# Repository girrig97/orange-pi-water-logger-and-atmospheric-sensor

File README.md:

# Orange Pi Water Logger

This starter project logs water-condition readings to a CSV file on the Orange Pi microSD card every 6 hours.

Variant branch: this branch includes shared logger code for Orange Pi Zero 3 and Orange Pi 5 Max. The EC25-AU cellular modem, SMS alerts, server status updates, and daily status reporting are optional and are skipped automatically when no modem/SIM is detected. See [docs/orange-pi-5-max-ec25-au.md](docs/orange-pi-5-max-ec25-au.md).

On the cellular branch, SMS alert recipients can be changed from the Android app using `Get SMS Numbers` and `Save SMS Numbers`.

## Design brief

Build a field-ready freshwater monitoring recorder that can run unattended from a USB power bank, store week-by-week CSV logs on microSD, and remain usable even when individual probes or optional hardware are disconnected.

Core requirements:

- Support both Orange Pi Zero 3 and Orange Pi 5 Max as the main logger.
- Use a Raspberry Pi Pico or Pico W as the always-on low-power time and power controller.
- Power the Orange Pi only when needed for scheduled logging, download mode, pairing mode, or manual checks.
- Record freshwater sensor data every 6 hours by default.
- Switch to hourly recording when barometric pressure is low or dropping quickly.
- Store records on the Orange Pi microSD card as weekly CSV files.
- Keep logging partial records if a sensor is damaged, disconnected, or not installed.
- Tag failed sensor reads with clear status values instead of stopping the logger.
- Build a sensor baseline from early successful readings so missing optional sensors do not create repeated fault alerts.
- Allow field access from an Android phone over Bluetooth for status, time sync, live readings, CSV downloads, SMS number settings, signal checks, and test SMS.
- Make cellular reporting optional. If no EC25-AU modem or usable SIM is detected, skip SMS work and continue normal logging.
- Send optional daily SMS status, server updates, and unsafe-water alerts when the EC25-AU modem is installed and ready.

Field-use behavior:

- Power-on should automatically start the correct mode without terminal access.
- Normal wake: Pico powers the Orange Pi, the logger writes one row, sends the next interval to the Pico, syncs data, and shuts down.
- Short button press: Pico starts download mode and keeps the Orange Pi awake for Bluetooth access.
- Long button hold: Pico starts pairing mode.
- 10-second hold while awake: manual power-off fallback.
- After Bluetooth download or resume, mode markers are cleared so the next wake returns to unattended logging.

Reliability considerations:

- CSV writes are flushed and fsynced.
- Weekly CSV files reduce the impact of single-file corruption.
- The UART link between Orange Pi and Pico is required for adaptive wake timing, but logger shutdown still continues if the UART notification fails.
- All grounds must be common.
- Orange Pi GPIO and ADS1115 inputs must stay within 3.3V logic/input limits.
- Probe modules need calibration before readings should be treated as meaningful.
- The enclosure, cable glands, connectors, and sensor electronics must be protected against water ingress and condensation.

## Sensors included

- pH
- TDS
- Turbidity
- DS18B20 temperature
- ORP
- Dissolved oxygen
- Ammonium ISE
- BME280 ambient temperature, humidity, and pressure

## Calculated values

- EC from TDS
- Estimated salinity
- Water clarity percent
- Dissolved oxygen saturation percent
- Toxic ammonia NH3 estimate from ammonium, pH, and temperature
- Ammonia risk label
- Overall water score and condition label
- Ambient dew point
- Air/water temperature difference
- Adaptive next logging interval from barometric pressure

## Materials

Core computer and power:

| Qty | Item | Notes |
| ---: | --- | --- |
| 1 | Orange Pi Zero 3 or Orange Pi 5 Max | Main logger, stores CSV on microSD |
| 1 | microSD card | 16GB or larger recommended |
| 1 | Raspberry Pi Pico or Pico W | Low-power timer and download-mode button controller |
| 1 | USB power bank | 10,000mAh minimum; larger is better |
| 1 | 5V relay or MOS power-switch module | Pico-controlled switch for Orange Pi 5V; rated at least 3A, preferably 5A |
| 1 | DS3231 RTC module | Keeps accurate time for the Pico controller |
| 1 | Momentary self-reset illuminated button | Use `NO` and `C` for the button signal; LED terminals are separate |
| 1 | Weatherproof enclosure | Large enough for Orange Pi, Pico, ADCs, and wiring |

Sensor and interface modules:

| Qty | Item | Notes |
| ---: | --- | --- |
| 2 | ADS1115 ADC modules | I2C analog inputs for Orange Pi |
| 1 | pH sensor board and BNC pH probe | Analog output to ADS1115 |
| 1 | TDS sensor meter V1.0 board and probe | Analog output to ADS1115 |
| 1 | Turbidity sensor module and probe | Analog output to ADS1115 |
| 1 | Waterproof DS18B20 temperature probe | Digital 1-Wire temperature |
| 1 | ORP sensor module and BNC ORP probe | Analog output to ADS1115 |
| 1 | Gravity analog dissolved oxygen sensor kit | Analog output to ADS1115 |
| 1 | NH4+ ammonium ISE probe | BNC probe |
| 1 | High-impedance ISE interface amplifier | Required between NH4+ probe and ADS1115 |
| 1 | BME280 I2C sensor module | Ambient air temperature, humidity, and barometric pressure |

Wiring and protection:

| Qty | Item | Notes |
| ---: | --- | --- |
| 1 | 4.7k resistor | DS18B20 data pull-up to 3.3V |
| Assorted | Jumper wires or hookup wire | Use reliable connectors for field use |
| Assorted | Screw terminals or waterproof connectors | Makes sensor replacement easier |
| Assorted | Heat shrink tubing | Strain relief and insulation |
| Assorted | Cable glands | For waterproof enclosure cable exits |
| As needed | Voltage divider resistors or level shifters | Required if sensor analog output can exceed 3.3V |
| 2 | UART link wires between Orange Pi and Pico | Required for download button requests and adaptive wake timing |
| Optional | Small fuse or resettable polyfuse | Protection on 5V power line |
| Optional | Desiccant pack | Helps reduce moisture in enclosure |

Calibration and maintenance:

| Qty | Item | Notes |
| ---: | --- | --- |
| 1 set | pH buffer solutions | pH 4.00, 7.00, and 10.00 |
| 1 | TDS calibration solution | Common examples: 342ppm or 1000ppm |
| 1 | ORP calibration solution | Match your ORP probe/module instructions |
| 1 | Dissolved oxygen calibration supplies | Follow Gravity DO kit instructions |
| 1 set | NH4+ ISE calibration standards | At least two known concentrations |
| 1 | Distilled or deionized water | Rinsing probes between calibration steps |
| Optional | Cleaning/storage solutions | Especially for pH, ORP, DO, and ISE probes |

## Hardware shape

Use two ADS1115 ADC boards on the Orange Pi I2C header. The code auto-detects likely I2C buses for Orange Pi Zero 3 and Orange Pi 5 Max. Set `I2C_BUS_NUMBER` only if you want to force a specific bus.

## Wiring diagram

PCB carrier design notes are in [docs/pcb-carrier-design-brief.md](docs/pcb-carrier-design-brief.md).
The first Zero 3 KiCad carrier scaffold is in [hardware/zero3-carrier](hardware/zero3-carrier).

Key things to double-check before powering on:

- The 5V power-switch module input connects to the USB power bank 5V, not to a Pico GPIO pin.
- The 5V power-switch module GND is on the common ground bus.
- Pico `GP15` drives only the power-switch trigger / enable / signal / `IN` pin.
- Pico `GP14` connects only to the download button, not to the power switch.
- ADS1115 #1 has `ADDR -> GND` for address `0x48`.
- ADS1115 #2 has `ADDR -> 3.3V` for address `0x49`.
- Any sensor analog output above 3.3V needs level scaling before the ADS1115 input.

The numbered badges in the image match the legend table below. Recheck the power-switch section carefully before building, because relay and MOS boards use different terminal names.

Corrected numbered wiring:

| Number | Correct connection |
| --- | --- |
| 1 | USB-C/power-bank 5V to the PCB input; protected 5V feeds Pico VSYS and the MOSFET switch input |
| 2 | Common GND bus to Pico GND, power-switch GND, Orange Pi GND, ADC GND, sensor GND |
| 3 | Pico `GP15` to power-switch trigger/enable input |
| 4 | Pico `GP14` to button `NO`; button `C` to common GND |
| 5 | Pico `GP4` to DS3231 SDA |
| 6 | Pico `GP5` to DS3231 SCL |
| 7 | Pico `3V3` to DS3231 VCC |
| 8 | MOSFET switched 5V output to Orange Pi 5V input, pin 2 or 4 |
| 9 | Power-switch output/common GND to Orange Pi GND, pin 6 |
| 10 | Orange Pi pin 1 `3.3V` to ADS1115 VDD and DS18B20 VCC |
| 11 | Orange Pi pin 3 SDA to both ADS1115 SDA pins |
| 12 | Orange Pi pin 5 SCL to both ADS1115 SCL pins |
| 13 | Orange Pi pin 7 PC9/GPIO7 to DS18B20 data, with 4.7k pull-up to 3.3V |
| 14 | ADS1115 #1 A0 to pH analog output |
| 15 | ADS1115 #1 A1 to TDS analog output |
| 16 | ADS1115 #1 A2 to turbidity analog output |
| 17 | ADS1115 #1 A3 to ORP analog output |
| 18 | ADS1115 #2 A0 to dissolved oxygen analog output |
| 19 | ADS1115 #2 A1 to ammonium ISE amplifier analog output |
| 20 | ADS1115 #2 A2 spare |
| 21 | ADS1115 #2 A3 spare |

Corrected wiring view:

```text
                                  USB POWER BANK
                                5V OUT      GND
                                  |          |
                                  |          +-------------------- COMMON GND BUS
                                  |                               |
                                  v                               |
                    +-----------------------------+               |
                    | Raspberry Pi Pico / Pico W  |               |
                    |                             |               |
                    | VSYS/USB <- 5V power bank   |               |
                    | GND ------ COMMON GND BUS --+               |
                    | GP15 ---- power enable ----------------+    |
                    | GP14 ---- button NO/C ---- GND          |    |
                    | GP4  ---- DS3231 SDA                   |    |
                    | GP5  ---- DS3231 SCL                   |    |
                    | 3V3  ---- DS3231 VCC                   |    |
                    +-----------------------------+           |    |
                                                              |    |
                                  +---------------------------+    |
                                  v                                |
                         +------------------+                      |
                         | 5V POWER SWITCH   |                      |
                         | TRIG/EN <- GP15  |                      |
                         | IN+ <- bank 5V   |                      |
                         | IN- <- GND bus --+----------------------+
                         | OUT+ -> OPi 5V   |
                         | OUT- -> OPi GND  |
                         +------------------+
                                  |
                                  v
                    +-----------------------------+
                    | Orange Pi Zero 3            |
                    | Pin 2/4 5V <- switched 5V   |
                    | Pin 6 GND  -> common GND    |
                    | Pin 1 3.3V -> 3.3V rail     |
                    | Pin 3 SDA  -> I2C SDA rail  |
                    | Pin 5 SCL  -> I2C SCL rail  |
                    | Pin 7 PC9  -> DS18B20 DATA  |
                    +-----------------------------+
                         |        |        |
                         |        |        +---------------- I2C SCL rail
                         |        +------------------------- I2C SDA rail
                         +---------------------------------- 3.3V rail

      3.3V rail ----------------+----------------------+----------------------+
                                |                      |                      |
                                v                      v                      v
                    +-------------------+  +----------------------+  +----------------------+
                    | ADS1115 #1        |  | ADS1115 #2           |  | DS18B20 temp probe   |
                    | ADDR -> GND       |  | ADDR -> 3.3V/VDD     |  | Red/VCC -> 3.3V      |
                    | address 0x48      |  | address 0x49         |  | Black/GND -> GND     |
                    | VDD -> 3.3V       |  | VDD -> 3.3V          |  | Yellow/DATA -> OPi 7 |
      GND bus ---->| GND -> GND        |  | GND -> GND           |  | 4.7k DATA -> 3.3V    |
      SDA rail --->| SDA -> OPi pin 3   |  | SDA -> OPi pin 3     |  +----------------------+
      SCL rail --->| SCL -> OPi pin 5   |  | SCL -> OPi pin 5     |
                    | A0 <- pH AO        |  | A0 <- DO AO          |
                    | A1 <- TDS AO       |  | A1 <- NH4 ISE AO     |
                    | A2 <- turbidity AO |  | A2 spare             |
                    | A3 <- ORP AO       |  | A3 spare             |
                    +-------------------+  +----------------------+
                              ^     ^     ^     ^            ^          ^
                              |     |     |     |            |          |
                              |     |     |     |            |          |
       +----------------------+     |     |     |            |          |
       |                            |     |     |            |          |
+-------------+              +-------------+ +-------------+ +-------------+ +------------------+
| pH module   |              | TDS module  | | Turbidity   | | ORP module  | | Gravity DO       |
| VCC -> 5V*  |              | VCC -> 5V*  | | VCC -> 5V*  | | VCC -> 5V*  | | VCC -> 3.3-5V*   |
| GND -> GND  |              | GND -> GND  | | GND -> GND  | | GND -> GND  | | GND -> GND       |
| AO -> A0    |              | AO -> A1    | | AO -> A2    | | AO -> A3    | | AO -> ADS #2 A0  |
| BNC -> probe|              | Probe socket| | Probe socket| | BNC -> probe| | Probe socket     |
+-------------+              +-------------+ +-------------+ +-------------+ +------------------+

                          +--------------------------+
                          | NH4+ ISE interface amp   |
                          | VCC -> module requirement|
                          | GND -> common GND        |
                          | BNC -> NH4+ ISE probe    |
                          | AO  -> ADS1115 #2 A1     |
                          +--------------------------+

                          +--------------------------+
                          | DS3231 RTC module        |
                          | VCC -> Pico 3V3          |
                          | GND -> common GND        |
                          | SDA -> Pico GP4          |
                          | SCL -> Pico GP5          |
                          +--------------------------+

                          +--------------------------+
                          | Momentary button         |
                          | NO -> Pico GP14          |
                          | C  -> common GND         |
                          +--------------------------+

* If a module's analog output can exceed 3.3V, add a voltage divider or level
  scaling before the ADS1115 input.
```

All grounds must be common:

```text
Power bank GND
Pico GND
power-switch GND
Orange Pi GND
ADS1115 GND
sensor module GND
DS3231 GND
DS18B20 GND
```

Do not power the Orange Pi directly from a Pico pin. The Pico only controls the relay/MOS power-switch trigger input.

### Power switch wiring options

The code expects a simple active-high control signal:

```text
Pico GP15 HIGH -> Orange Pi power on
Pico GP15 LOW  -> Orange Pi power off
```

For a relay module, use the relay contacts to switch the Orange Pi 5V positive line:

| Relay terminal | Connect to |
| --- | --- |
| `VCC` | module supply voltage, usually 5V unless your board says otherwise |
| `GND` | common GND |
| `IN`, `SIG`, or `TRIG` | Pico `GP15` |
| `COM` | USB power bank 5V |
| `NO` | Orange Pi 5V pin 2 or 4 |
| `NC` | leave unused |

Use `NO`, not `NC`, so the Orange Pi is normally off until the Pico enables it.

For a MOS switch board, use the switched output terminals:

| MOS switch terminal | Connect to |
| --- | --- |
| `VIN+`, `V+`, or `DC+` | USB power bank 5V |
| `VIN-`, `V-`, or `DC-` | common GND |
| `TRIG`, `PWM`, `IN`, or `EN` | Pico `GP15` |
| `VOUT+`, `OUT+`, or `LOAD+` | Orange Pi 5V pin 2 or 4 |
| `VOUT-`, `OUT-`, or `LOAD-` | Orange Pi GND |

Some MOS boards are low-side switches, meaning they only switch the ground side. They can work for testing, but a relay contact or high-side switch is safer for field use because it avoids back-powering through UART or sensor wires.

## Module wiring summary

| Module | Power | Ground | Signal to Orange Pi/ADC | Probe connection |
| --- | --- | --- | --- | --- |
| pH board | 5V or module spec | common GND | AO to ADS1115 #1 A0 | pH BNC probe |
| TDS board | 5V or module spec | common GND | AO to ADS1115 #1 A1 | TDS probe socket |
| Turbidity board | 5V or module spec | common GND | AO to ADS1115 #1 A2 | turbidity probe socket |
| ORP board | 5V or module spec | common GND | AO to ADS1115 #1 A3 | ORP BNC probe |
| Gravity dissolved oxygen board | 3.3V-5V, module spec | common GND | AO to ADS1115 #2 A0 | DO probe socket |
| NH4+ ISE interface amplifier | module spec | common GND | AO to ADS1115 #2 A1 | NH4+ ISE BNC probe |
| DS18B20 waterproof temp probe | Orange Pi 3.3V | common GND | DATA to Orange Pi pin 7 | built in |
| BME280 ambient sensor | Orange Pi 3.3V | common GND | SDA pin 3, SCL pin 5 | air temp, humidity, pressure |
| ADS1115 #1 | Orange Pi 3.3V | common GND | SDA pin 3, SCL pin 5 | A0-A3 analog inputs |
| ADS1115 #2 | Orange Pi 3.3V | common GND | SDA pin 3, SCL pin 5 | A0-A3 analog inputs |
| DS3231 RTC | Pico 3.3V | common GND | SDA GP4, SCL GP5 | none |
| 5V relay or MOS power switch | power bank 5V input | common GND | trigger/EN from Pico GP15 | switched 5V to Orange Pi |
| Momentary button switch | none | `C` to common GND | `NO` to Pico GP14 | none |
| Required UART link | Orange Pi 3.3V UART logic | common GND | Orange Pi TX to Pico GP1/RX, Orange Pi RX to Pico GP0/TX | download mode and adaptive wake timing |

## Orange Pi Zero 3 header wiring

| Orange Pi physical pin | Function | Connect to |
| --- | --- | --- |
| Pin 1 | 3.3V | ADS1115 VDD, DS18B20 VCC |
| Pin 3 | I2C3 SDA | ADS1115 #1 SDA, ADS1115 #2 SDA |
| Pin 5 | I2C3 SCL | ADS1115 #1 SCL, ADS1115 #2 SCL |
| Pin 6 | GND | ADS1115 GND and all sensor GND wires |
| Pin 7 | GPIO PC9 | DS18B20 data |
| Pin 2 or 4 | 5V | Sensor boards that require 5V input |

Add a 4.7k resistor between DS18B20 data and 3.3V.

## ADS1115 address setup

| ADC board | ADDR pin | I2C address |
| --- | --- | --- |
| ADS1115 #1 | GND | `0x48` |
| ADS1115 #2 | VDD | `0x49` |

## ADS1115 sensor wiring

| Sensor | ADC input |
| --- | --- |
| pH | ADS1115 #1 A0 |
| TDS | ADS1115 #1 A1 |
| Turbidity | ADS1115 #1 A2 |
| ORP | ADS1115 #1 A3 |
| Dissolved oxygen | ADS1115 #2 A0 |
| Ammonium ISE interface | ADS1115 #2 A1 |

The ammonium ISE needs a high-impedance ISE interface board. Do not connect the electrode directly to the ADC.

Important: if the ADS1115 boards are powered from 3.3V, every analog input must stay between 0V and 3.3V. If a sensor board outputs 0-5V, use a voltage divider or level-scaling circuit before the ADS1115 input.

## Orange Pi setup

Enable I2C3:

```bash
sudo orangepi-config
```

Then go to `System`, `Hardware`, enable `ph-i2c3`, save, and reboot.

After reboot, check the ADC boards. For a Zero 3 this is usually bus 3; for a 5 Max use the bus you enabled, or run `ls /dev/i2c-*` and scan the likely buses:

```bash
sudo apt update
sudo apt install -y i2c-tools python3-smbus
i2cdetect -y 3
```

You should see:

```text
0x48
0x49
```

The code reads ADS1115 #1 at `0x48` and ADS1115 #2 at `0x49`. If `I2C_BUS_NUMBER` is unset, it auto-detects likely Orange Pi I2C buses.

## BME280 ambient sensor

Wire the BME280 to the same Orange Pi I2C bus as the ADS1115 boards:

| BME280 pin | Orange Pi header function |
| --- | --- |
| VCC/VIN | Pin 1 `3.3V` |
| GND | Pin 6 `GND` |
| SDA | Pin 3 `I2C SDA` |
| SCL | Pin 5 `I2C SCL` |

The BME280 usually appears at `0x76` or `0x77`. The logger tries both.

Install the Python libraries:

```bash
sudo apt install -y python3-pip
pip3 install smbus2 RPi.bme280 pyserial
```

The CSV adds:

```text
air_temperature_c
air_humidity_percent
air_pressure_hpa
dew_point_c
air_water_temp_difference_c
next_interval_seconds
```

## Sensor fault handling

If a sensor is damaged, disconnected, or not responding, the logger keeps running. The affected raw value and dependent calculated values are left blank in the CSV, and the matching status column explains why.

Status columns include:

```text
temperature_status
ph_status
tds_status
turbidity_status
orp_status
dissolved_oxygen_status
ammonium_ise_status
air_sensor_status
```

Common status tags:

| Tag | Meaning |
| --- | --- |
| `ok` | Sensor reading worked |
| `ds18b20_not_found` | Temperature probe was not detected |
| `ds18b20_crc_failed` | Temperature probe responded with a bad checksum |
| `ads1115_0x48_not_found_or_i2c_failed` | First ADS1115 board did not respond |
| `ads1115_0x49_not_found_or_i2c_failed` | Second ADS1115 board did not respond |
| `ads1115_0x48_channel_0_read_failed` | Specific ADC channel read failed |
| `partial_read_failure` | Some samples worked and some failed |
| `bme280_not_found_or_not_responding` | Ambient air sensor did not respond |
| `bme280_library_missing` | BME280 Python library is not installed |

Example: if the ORP probe board is disconnected, `orp_voltage` and `orp_mv` will be blank, while `orp_status` will explain the fault.

## Adaptive low-pressure logging

By default:

```text
pressure >= 1000 hPa -> next recording in 6 hours
pressure < 1000 hPa  -> next recording in 1 hour
pressure drop >= 6 hPa over recent 24h -> next recording in 1 hour
```

The Orange Pi writes the next interval to:

```text
/home/orangepi/water-logger/records/next_interval_seconds.txt
```

The UART link is required. The Pico uses it to request download mode, and after each reading the Orange Pi sends the next wake interval back to the Pico:

```text
NEXT_INTERVAL=3600
```

or:

```text
NEXT_INTERVAL=21600
```

Required UART wiring:

| Signal | Connect |
| --- | --- |
| Orange Pi UART TX | Pico GP1/RX |
| Orange Pi UART RX | Pico GP0/TX |
| Orange Pi GND | Pico GND |

The logger records the row even if this UART link is unavailable, then logs a warning and continues shutdown so the power bank is not drained. The Pico treats a missing `NEXT_INTERVAL` as a fault and retries in 1 hour. The code defaults to Orange Pi serial port `/dev/ttyS5`. If your enabled UART appears under another name, set:

```bash
export PICO_SERIAL_PORT=/dev/ttyS1
```

For I2C, auto-detection usually avoids board-specific edits. To force a bus:

```bash
export I2C_BUS_NUMBER=3   # common Zero 3 setup
export I2C_BUS_NUMBER=5   # example 5 Max setup
```

## microSD record path

Records are stored beside the project in a `records` folder. The logger starts a new CSV file each ISO calendar week to keep files smaller and reduce the impact of any single-file corruption.

If the project is copied to:

```text
/home/orangepi/water-logger
```

weekly CSV files will be created like:

```text
/home/orangepi/water-logger/records/water_conditions_2026_week_20.csv
/home/orangepi/water-logger/records/water_conditions_2026_week_21.csv
```

The download-mode marker lives in the same folder:

```text
/home/orangepi/water-logger/records/DOWNLOAD_MODE
```

## Run

```bash
python3 water_logger.py
```

The CSV files will be created as weekly files:

```text
water_conditions_YYYY_week_WW.csv
```

on the microSD card.

## Low power mode

For USB power bank use, run one reading at a time:

```bash
python3 water_logger.py --once
```

Then schedule it every 6 hours with a systemd timer or cron job. This avoids keeping the Python program awake all day, although the Orange Pi itself is still powered unless you add timed power-control hardware.

Example cron line:

```cron
0 */6 * * * /usr/bin/python3 /home/orangepi/water_logger.py --once
```

For much longer battery life, use a timer power switch, RTC power module, or small microcontroller to turn the Orange Pi on every 6 hours, let it log once, then shut it down.

With timed power hardware, run:

```bash
python3 water_logger.py --once --shutdown-after
```

## Pico power controller

Use `pico_power_controller.py` on a Raspberry Pi Pico or Pico W to switch Orange Pi power.

| Pico pin | Connect to |
| --- | --- |
| GP15 | On-board MOSFET/load-switch gate-driver input |
| GP14 | Momentary button `NO`; button `C` to GND |
| GP0/TX | Orange Pi UART RX |
| GP1/RX | Orange Pi UART TX |
| GP4 | DS3231 SDA |
| GP5 | DS3231 SCL |
| GP13 | Strongly recommended: Orange Pi ready/shutdown GPIO |
| 3V3 | DS3231 VCC |
| GND | DS3231 GND, button `C`, MOSFET gate-driver GND |
| VSYS or 5V USB input | Always-on protected 5V from the board USB-C input |

One USB-C PD input can power both the Pico and Orange Pi Zero 3. Wire it as:

```text
USB-C PD input -> PD sink controller -> negotiated 9V rail
USB-C PD input -> PD sink controller -> buck regulator -> Pico always-on 5.1V/VSYS
USB-C PD input -> PD sink controller -> buck regulator -> high-side MOSFET -> Orange Pi 5V input
```

The Pico stays powered all the time. The Orange Pi 5V input is powered only
through the MOSFET/load-switch path. For the PCB version, use a USB-C PD sink
controller and a 5A buck regulator so the board can request 9V from the power
bank and generate its own stable 5.1V rail. A 30W or larger USB-C PD power bank
is the sensible minimum for the Zero 3 build.

Normal mode:

- Pico powers the Orange Pi every 6 hours.
- Orange Pi runs `water_logger.py --once --shutdown-after`.
- Pico cuts Orange Pi power after the logging window.

Wire the Orange Pi ready/shutdown GPIO to Pico `GP13` if possible. Without it, the Pico uses the full scheduled safety window before cutting power; with it, the Pico can cut power shortly after Linux has finished and shut down cleanly.

Download mode:

- Press the Pico button once and release.
- Pico powers the Orange Pi, keeps it on, and sends a UART download-mode request.
- The status LED flashes slowly while the Orange Pi is awake for download mode.
- Download the CSV over Bluetooth or WiFi.
- Hold the button for 10 seconds while awake to cut power manually.
- A 1-hour timeout turns it off as a fallback.

Pairing mode:

- Hold the Pico button for 2 seconds while the logger is asleep.
- Pico powers the Orange Pi, keeps it on, and sends a UART pairing-mode request.
- The status LED flashes quickly while the Orange Pi is awake for pairing mode.
- The Orange Pi makes Bluetooth discoverable and pairable, then starts the same Bluetooth records server.
- Pair your phone, then use the Android app or Bluetooth terminal commands.

The momentary self-reset button terminals are:

| Button terminal | Use |
| --- | --- |
| `NO` | Connect to Pico `GP14` |
| `C` | Connect to common GND |
| `NC` | Leave unused |
| `A` or `+` | LED positive, optional |
| `LED` or `-` | LED negative, optional |

Use `NO` and `C`, so the Pico input is normally open and only connects to GND while pressed. Do not use the self-locking/latching version for this behavior.

The button LED is separate from the button switch. The code flashes `STATUS_LED_PIN`, which defaults to the Pico onboard LED on `GP25`. To flash the button's built-in LED instead, change `STATUS_LED_PIN` in `pico_power_controller.py` to a spare Pico GPIO and wire the LED terminals according to the voltage rating of your button LED. If the LED is bare 3V style, use a current-limiting resistor, for example 330 ohms. If it is a 5V/12V/24V button LED, do not connect it directly to a Pico GPIO unless the listing says it is safe at 3.3V.

Button behavior summary:

| Button action | Result | LED pattern |
| --- | --- | --- |
| Short press and release | Download mode | Slow flash |
| Hold for 2 seconds from sleep | Bluetooth pairing mode | Fast flash |
| Hold for 10 seconds while awake | Manual power-off fallback | LED off after power cut |

The button is the normal way to enter download or pairing mode. As a fallback, you can manually create this empty file before boot:

```text
DOWNLOAD_MODE
```

For pairing mode fallback, create:

```text
PAIRING_MODE
```

When the boot wrapper sees the Pico request, `records/DOWNLOAD_MODE`, or `records/PAIRING_MODE`, it starts the Bluetooth serial download server instead of doing the normal unattended log-and-shutdown cycle.

## Boot service for timed power

Copy this project to:

```text
/home/orangepi/water-logger
```

Then install the boot service:

```bash
sudo cp orange_pi_boot_logger.service /etc/systemd/system/
sudo systemctl enable orange_pi_boot_logger.service
```

When the Pico powers the Orange Pi, the service runs one reading and shuts the Orange Pi down unless the microSD records folder contains `DOWNLOAD_MODE`.

If `DOWNLOAD_MODE` or `PAIRING_MODE` exists, the boot wrapper starts a Bluetooth serial download server instead of shutting down. `PAIRING_MODE` also asks BlueZ to make the Orange Pi Bluetooth adapter discoverable and pairable.

Bluetooth commands:

| Command | What it does |
| --- | --- |
| `status` | Shows weekly file count, latest file, total size, and download-mode state |
| `latest` | Sends the newest CSV row |
| `settime 2026-05-12T14:30:00+10:00` | Sets Orange Pi time from your phone, then logs a fresh reading |
| `log` | Logs one fresh reading using the current Orange Pi time |
| `live` | Streams unsaved live readings every 5 seconds |
| `stop` | Stops live reading stream |
| `sms` | Shows configured SMS alert recipient numbers |
| `setsms +61400111222,+61400999888` | Sets SMS alert recipient numbers |
| `clearsms` | Clears SMS alert recipient numbers |
| `resetbaseline` | Clears the sensor-failure baseline after sensor repair or reconfiguration |
| `signal` | Shows EC25 network generation and signal level on the cellular branch |
| `testsms` | Sends a test SMS to configured recipients on the cellular branch |
| `download` | Sends the newest weekly CSV, deletes `DOWNLOAD_MODE`, syncs, and shuts down |
| `download all` | Sends all weekly CSV files, deletes `DOWNLOAD_MODE`, syncs, and shuts down |
| `resume` | Deletes `DOWNLOAD_MODE`/`PAIRING_MODE` and shuts down without downloading |

That means after a successful Bluetooth `download`, the next Pico wake returns to normal 6-hour logging automatically.

## Download logs from a phone over Bluetooth

You can use the included Android companion app in `android-app/`, or use a generic Bluetooth serial terminal.

### Android companion app

The Android app provides buttons for:

```text
Connect
System Status
Record Count
List Record Times
Latest Reading
Start Live Readings
Stop Live Readings
Sync Time + Log
Log Fresh Reading
Download Latest Week
Download All Weeks
Resume Normal Logging
```

The app connects to the Orange Pi Bluetooth serial service and sends the same commands documented below.

To build the APK:

1. Push the project to GitHub.
2. Open the repository on GitHub.
3. Go to `Actions`.
4. Run `Build Android APK`, or wait for it to run after changes to `android-app/`.
5. Download the `water-logger-companion-debug-apk` artifact.
6. Install `app-debug.apk` on your Android phone.

On the phone, you may need to allow:

```text
Install unknown apps
Bluetooth permission
```

Before opening the app, pair your phone with the Orange Pi in Android Bluetooth settings.

### Bluetooth terminal fallback

Use an Android Bluetooth serial terminal app. Search for one of these:

```text
Serial Bluetooth Terminal
Bluetooth Terminal
RFCOMM Bluetooth terminal
```

Phone workflow:

1. Press the Pico download-mode button.
2. Wait for the Orange Pi to boot.
3. Pair your phone with the Orange Pi through Bluetooth settings.
4. Open the Bluetooth terminal app and connect to `OrangePi Water Records`.
5. Send `status` to check the connection.
6. Send `download` for the newest weekly CSV, or `download all` for every weekly CSV.

After `download` or `download all`, the Orange Pi deletes `DOWNLOAD_MODE`, syncs the microSD, shuts down, and the next Pico wake returns to normal logging.

The button request uses the required UART link from Pico to Orange Pi. As a fallback, you can also manually create this file before boot:

```text
records/DOWNLOAD_MODE
```

If your phone has not been paired before, hold the button for 2 seconds from sleep instead of short-pressing it. The fast LED flash means pairing mode is active. Pair the phone first, then open the Android app or Bluetooth terminal.

## Sync time from phone over Bluetooth

In download mode, the Orange Pi starts the Bluetooth command server before taking an extra download-mode reading. This lets your phone set the clock first so the new log row has true time.

Send this from the Bluetooth terminal:

```text
settime 2026-05-12T14:30:00+10:00
```

Use your actual phone time and timezone offset. For Brisbane/Australia standard time, the offset is usually:

```text
+10:00
```

After `settime`, the Orange Pi:

1. Sets its system clock.
2. Tries to write hardware clock time with `hwclock -w`.
3. Records one fresh sensor row.
4. Keeps Bluetooth open so you can send `download`.

Example field sequence:

```text
status
settime 2026-05-12T14:30:00+10:00
latest
download
```

If you only want to set time and take a fresh reading without downloading yet, send:

```text
settime 2026-05-12T14:30:00+10:00
```

If the time is already correct and you only want a fresh row:

```text
log
```

## Live readings

Live readings let you check the sensors without adding rows to the weekly CSV.

In the Android app, press:

```text
Start Live Readings
```

The Orange Pi streams one fresh unsaved reading every 5 seconds. Press:

```text
Stop Live Readings
```

to stop the stream.

From a Bluetooth terminal, use:

```text
live
```

and then:

```text
stop
```

Install Bluetooth serial support:

```bash
sudo apt install -y bluetooth bluez python3-bluez
sudo systemctl enable bluetooth
sudo systemctl start bluetooth
```

## Important

The pH, TDS, turbidity, ORP, dissolved oxygen, and ammonium calculations contain starter calibration values. You will need to calibrate each probe before trusting the numbers.

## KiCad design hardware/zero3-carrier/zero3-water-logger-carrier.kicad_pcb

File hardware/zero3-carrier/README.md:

# Orange Pi Zero 3 Water Logger Carrier PCB

This KiCad project is the first-pass PCB carrier for the Orange Pi Zero 3
version of the water logger.

Status: **ERC + DRC clean, fully routed by Freerouting, Gerbers exported under `fabrication/pcbway/`. Do not order without first reviewing the switching power supply layout against the TPS54531 reference design** — see `fabrication/pcbway/REVIEW-BEFORE-ORDER.md`.

The board is intended to act as a shield/carrier/interface board:

- Orange Pi Zero 3 connects through its 26-pin header.
- Raspberry Pi Pico plugs into 2 x 20 headers.
- DS3231, BME280, and ADS1115 boards can plug into module headers.
- Water sensors connect through labelled screw terminals or JST-style headers.
- An integrated high-side 5V MOSFET/load-switch section switches Orange Pi power.
- DS18B20 has a 4.7k pull-up footprint.

## Files

| File | Purpose |
| --- | --- |
| `zero3-water-logger-carrier.kicad_pro` | KiCad project |
| `zero3-water-logger-carrier.kicad_sch` | R1 schematic draft with PD, buck, switch, Pico, Orange Pi, ADC, sensor, RTC, and ambient headers |
| `zero3-water-logger-carrier.kicad_pcb` | Board outline, assigned footprints, schematic nets, and placement draft |
| `water_logger_generated.kicad_sym` | Local generated KiCad symbol library used by the schematic |
| `sym-lib-table` | Project symbol-library table for the generated `WL` library |
| `zero3-water-logger-carrier-pinout.csv` | Pin/net planning table |
| `selected-parts-bom.csv` | Selected revision-1 PD/buck/MOSFET parts and values |
| `fabrication-readiness.md` | PCBWay/Gerber readiness checklist |
| `generate_schematic.py` | Regenerates the KiCad schematic + symbol library + pinout CSV from the selected net plan |
| `generate_pcb.py` | Regenerates the KiCad PCB placement, net assignments, and dual-layer GND pours from the selected net plan |
| `route_with_freerouting.py` | One-command auto-routing: exports DSN, runs Freerouting, imports SES, refills zones, re-runs DRC |
| `validate_design.py` | ERC + DRC + pinout-CSV format gate; runs before committing PCB changes |
| `manual-routing-guide.md` | Step-by-step hand-routing instructions, including the required TPS54531 and high-side MOSFET datasheet routes |

Current schematic check: `kicad-cli sch erc` reports **0 violations**. Current
PCB DRC reports **0 violations** and **0 unconnected items** after
Freerouting routed all 83 signal/power nets. The full PCBWay upload package
(Gerbers, drill, schematic PDF, review checklist) is in
`fabrication/pcbway/`, also zipped as `fabrication/zero3-water-logger-carrier-R1.zip`.

## Current Placement

The R1 board file contains schematic-synced footprints and net assignments for:

- Orange Pi Zero 3 26-pin header.
- Raspberry Pi Pico 2 x 20 socket.
- ADS1115 #1 and #2 module headers.
- DS18B20, BME280, and DS3231 module headers.
- Six 3-pin analog sensor terminals: pH, TDS, turbidity, ORP, dissolved oxygen, and ammonium ISE amp.
- Download button header with switch contacts and optional LED terminals.
- Spare analog header for the unused ADS1115 #2 A2/A3 channels.
- 4.7k DS18B20 pull-up resistor.
- Integrated USB-C PD input, TPS54531 buck regulator, and high-side 5V MOSFET
  switch section.

The PCB is intentionally left unrouted. Route and review the power section in
KiCad before generating Gerbers. The CH224K package/pin mapping must be checked
against the exact part datasheet before assembly.

## Integrated 5V Switch

The board now plans for an on-board high-side 5V switch instead of an external
relay/MOSFET module.

Power path:

```text
USB-C PD input -> PD sink controller -> negotiated 9V rail
                -> buck regulator -> protected 5.1V rail
                                  -> Pico always-on VSYS/5V
                                  -> P-channel MOSFET -> switched 5V rail
```

Control path:

```text
Pico GP15 -> gate-driver transistor/MOSFET -> P-channel MOSFET gate
```

Default state is off. The P-channel MOSFET gate is pulled up to fused 5V. When
Pico GP15 goes high, the small gate-driver device pulls the P-channel gate low
and enables switched 5V to the Orange Pi.

Planned parts:

| Ref | Function | Requirement |
| --- | --- | --- |
| `J14` | USB-C PD input | USB-C 16-pin receptacle, HRO TYPE-C-31-M-12 class |
| `U1` | USB-C PD sink controller | CH224K, strapped for fixed 9V request |
| `D1` | VBUS TVS diode | USB/PD-rated input surge protection |
| `F1` | Input protection | Resettable fuse/polyfuse on negotiated PD input rail |
| `U2` | Buck regulator | TPS54531DDA 5A buck regulator |
| `L1` | Buck inductor | 4.7uH shielded inductor rated at least 6A |
| `D2` | Buck catch diode | CDBC540-G or equivalent 5A/40V Schottky |
| `CIN1`, `CIN2` | Buck/input capacitors | 4.7uF 50V X7R near `U2` |
| `CIN3` | Buck high-frequency bypass | 10nF 50V near `U2` |
| `COUT1`, `COUT2` | 5.1V output capacitors | 47uF low-ESR output capacitors |
| `RFB1`, `RFB2` | Buck feedback divider | TPS54531 example values: 10.2k / 1.96k |
| `REN1`, `REN2` | Buck enable divider | TPS54531 8V minimum input example values: 665k / 130k |
| `RCOMP1`, `CCOMP1`, `CCOMP2` | Buck compensation | TPS54531 example compensation network |
| `Q1` | High-side switch | AO4407A P-channel MOSFET, SOIC-8 |
| `Q2` | Gate driver | 2N7002 N-MOSFET, SOT-23, driven by Pico GP15 |
| `R2` | Gate pull-up | 100k from Q1 gate to fused 5V, keeps switch off |
| `R3` | Gate drive resistor | 1k between Pico GP15 and Q2 gate/base |
| `R4` | Driver pulldown | 100k from Q2 gate/base to GND |
| `C1` | Switched rail bulk cap | 470uF-1000uF, voltage rating at least 10V |

One USB-C port can power both boards. The Pico is connected to the protected
5.1V rail before the MOSFET so it stays awake. The Orange Pi Zero 3 is connected
only to the switched 5V rail after Q1 so the Pico can turn it off between logs.

Use a USB-C PD power bank or charger that can provide at least 30W. The target
PD profile is `9V 3A` or better, feeding a 5.1V buck rail. The TPS54531 design
uses an 8V minimum input example, so non-PD 5V fallback is not supported by this
revision.

Before ordering, verify the exact `J14`, `U1`, `U2`, `Q1`, and `Q2` pinouts
against the chosen footprints. PD controllers, buck regulators, USB-C
connectors, and MOSFET pin order are not universal.

## Revision 1 Scope

The first PCB order should keep modules replaceable:

- Socket the Pico.
- Socket the ADS1115 modules.
- Socket the DS3231 module.
- Use external sensor boards for pH, TDS, turbidity, ORP, DO, and ammonium ISE.
- Keep the EC25 modem off this PCB.

Do not order until:

- Schematic symbols and PCB footprints for the selected PD/buck/MOSFET parts
  are placed and reviewed.
- Terminal block pitch is chosen.
- The Zero 3 header clearance is checked against the actual board.
- The schematic ERC and PCB DRC pass.
- PCB DRC reports zero unconnected items after routing.
- Gerbers are opened in an independent Gerber viewer.

## Recommended PCBWay Settings

- 2 layers.
- FR-4.
- 1.6mm thickness.
- 1oz copper minimum; 2oz preferred if switching Orange Pi current on-board.
- Green solder mask unless you prefer another colour.
- HASL lead-free or ENIG.
- Use conservative rules: 0.20mm trace/space for signals, much wider for 5V/GND.

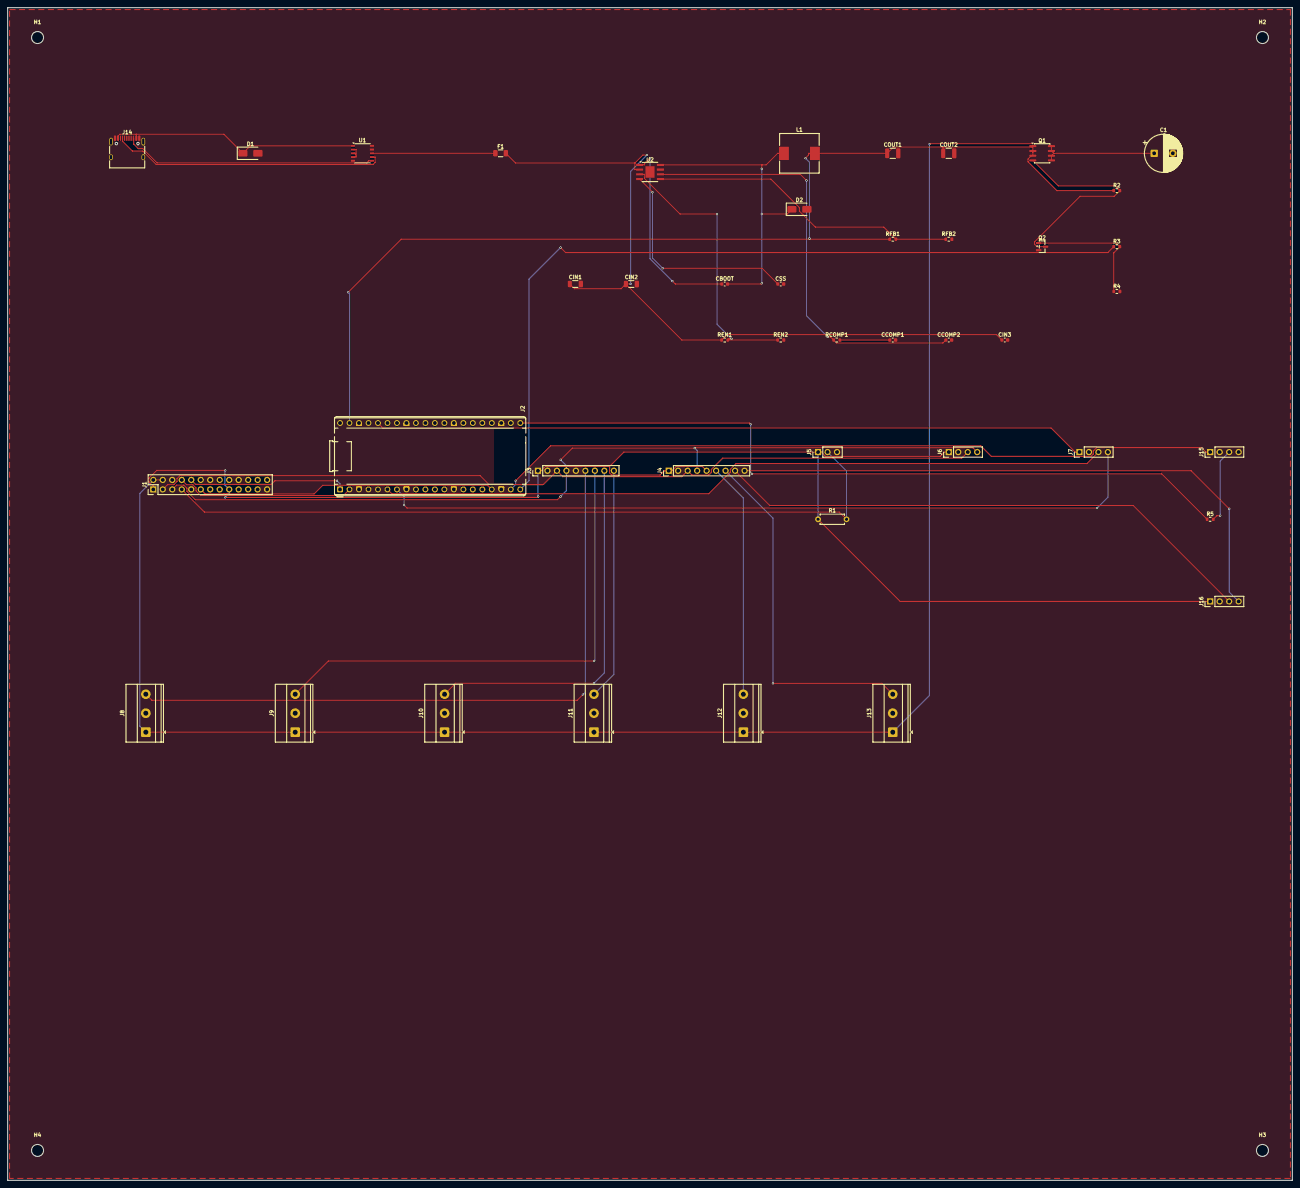
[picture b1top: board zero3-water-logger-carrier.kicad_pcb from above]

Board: 2 copper layers, 344.0 x 314.0 mm, 48 parts (0 on the bottom side), 40 nets.

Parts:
C1: 470uF-1000uF 10V; CP_Radial_D10.0mm_P5.00mm
CBOOT: 100nF; C_0603_1608Metric
CCOMP1: 2200pF; C_0603_1608Metric
CCOMP2: 22pF; C_0603_1608Metric
CIN1, CIN2: 4.7uF 50V; C_1206_3216Metric
CIN3: 10nF 50V; C_0603_1608Metric
COUT1, COUT2: 47uF 10V; C_1210_3225Metric
CSS: 10nF; C_0603_1608Metric
D1: VBUS TVS; D_SMA
D2: 5A 40V Schottky; D_SMA
F1: 3A-5A polyfuse; Fuse_1206_3216Metric
H1, H2, H3, H4: MountingHole_3.2mm_M3
J1: Orange Pi Zero 3 26-pin; PinHeader_2x13_P2.54mm_Vertical
J2: Raspberry Pi Pico socket; RaspberryPi_Pico_Common_THT
J3: ADS1115 #1 0x48; PinHeader_1x09_P2.54mm_Vertical
J4: ADS1115 #2 0x49; PinHeader_1x09_P2.54mm_Vertical
J5: DS18B20 water temp; PinHeader_1x03_P2.54mm_Vertical
J6: BME280 air sensor; PinHeader_1x04_P2.54mm_Vertical
J7: DS3231 RTC; PinHeader_1x04_P2.54mm_Vertical
J8: pH sensor; TerminalBlock_Phoenix_MKDS-1,5-3-5.08_1x03_P5.08mm_Horizont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
J9: TDS sensor; TerminalBlock_Phoenix_MKDS-1,5-3-5.08_1x03_P5.08mm_Horizont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
J10: Turbidity sensor; TerminalBlock_Phoenix_MKDS-1,5-3-5.08_1x03_P5.08mm_Horizont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
J11: ORP sensor; TerminalBlock_Phoenix_MKDS-1,5-3-5.08_1x03_P5.08mm_Horizont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
J12: Dissolved oxygen; TerminalBlock_Phoenix_MKDS-1,5-3-5.08_1x03_P5.08mm_Horizont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
J13: NH4 ISE amp; TerminalBlock_Phoenix_MKDS-1,5-3-5.08_1x03_P5.08mm_Horizont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
J14: USB-C PD input; USB_C_Receptacle_HRO_TYPE-C-31-M-12
J15: Download button; PinHeader_1x04_P2.54mm_Vertical
J16: Spare analog header; PinHeader_1x04_P2.54mm_Vertical
L1: 4.7uH >=6A; L_10.4x10.4_H4.8
Q1: AO4407A P-MOS high-side; SOIC-8_3.9x4.9mm_P1.27mm
Q2: 2N7002; SOT-23
R1: 4.7k; R_Axial_DIN0207_L6.3mm_D2.5mm_P7.62mm_Horizontal
R2, R4: 100k; R_0603_1608Metric
R3: 1k; R_0603_1608Metric
R5: 330R if 3.3V LED; R_0603_1608Metric
RCOMP1: 37.4k; R_0603_1608Metric
REN1: 665k; R_0603_1608Metric
REN2: 130k; R_0603_1608Metric
RFB1: 10.2k 1%; R_0603_1608Metric
RFB2: 1.96k 1%; R_0603_1608Metric
U1: CH224K PD sink 9V; SSOP-10_3.9x4.9mm_P1.00mm
U2: TPS54531DDA 5A buck; TI_SO-PowerPAD-8

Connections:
BUCK_BOOT: CBOOT.1, U2.1
BUCK_COMP: CCOMP2.1, RCOMP1.1, U2.6
BUCK_COMP_RC: CCOMP1.1, RCOMP1.2
BUCK_EN: REN1.2, REN2.1, U2.3
BUCK_FB: RFB1.2, RFB2.1, U2.5
BUCK_SS: CSS.1, U2.4
BUCK_SW: CBOOT.2, D2.1, L1.1, U2.8
BUTTON_LED_A: J15.3, R5.2
DO_AIN: J4.6, J12.3
FUSED_5V1: COUT1.1, COUT2.1, J2.39, L1.2, Q1.1, Q1.2, Q1.3, R2.1, RFB1.1
GND: C1.2, CCOMP1.2, CCOMP2.2, CIN1.2, CIN2.2, CIN3.2, COUT1.2, COUT2.2, CSS.2, D1.2, D2.2, J1.6, J1.9, J1.14, J1.20, J1.25, J2.3, J2.8, J2.13, J2.18, J2.23, J2.28, J2.33, J2.38, J3.2, J3.5, J4.2, J5.3, J6.2, J7.2, J8.2, J9.2, J10.2, J11.2, J12.2, J13.2, J14.A1, J14.A12, J14.B1, J14.B12, J14.SH, J15.2, J15.4, J16.2, Q2.2, R4.2, REN2.2, RFB2.2, U1.5, U1.9, U1.10, U2.7, U2.9
NH4_AIN: J4.7, J13.3
OPI_1WIRE: J1.7, J5.2, R1.2
OPI_3V3: J1.1, J1.17, J3.1, J4.1, J4.5, J5.1, J6.1, J16.1, R1.1
OPI_5V_SW: C1.1, J1.2, J1.4, J8.1, J9.1, J10.1, J11.1, J12.1, J13.1, Q1.5, Q1.6, Q1.7, Q1.8
OPI_READY: J1.11, J2.17
OPI_SCL: J1.5, J3.4, J4.4, J6.4
OPI_SDA: J1.3, J3.3, J4.3, J6.3
ORP_AIN: J3.9, J11.3
PD_CFG: U1.2, U1.3, U1.4
PD_FUSED: CIN1.1, CIN2.1, CIN3.1, F1.2, REN1.1, U2.2
PD_NEGOTIATED_VBUS: F1.1, U1.8
PH_AIN: J3.6, J8.3
PICO_3V3: J2.36, J7.1
PICO_GP4: J2.6, J7.3
PICO_GP5: J2.7, J7.4
PICO_GP14: J2.19, J15.1
PICO_GP15: J2.20, R3.1
PICO_LED_GP16: J2.21, R5.1
PWR_GATE: Q1.4, Q2.3, R2.2
Q2_GATE: Q2.1, R3.2, R4.1
SPARE_AIN2: J4.8, J16.3
SPARE_AIN3: J4.9, J16.4
TDS_AIN: J3.7, J9.3
TURB_AIN: J3.8, J10.3
UART_OPI_TX_PICO_RX: J1.8, J2.2
UART_PICO_TX_OPI_RX: J1.10, J2.1
USB_CC1: J14.A5, U1.7
USB_CC2: J14.B5, U1.6
USB_VBUS: D1.1, J14.A4, J14.A9, J14.B4, J14.B9, U1.1

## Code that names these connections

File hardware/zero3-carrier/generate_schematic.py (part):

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        "footprint": "Diode_SMD:D_SMA",
        "x": 58,
        "y": 35,
        "pins": [("1", "K", "USB_VBUS"), ("2", "A", "GND")],
    },
    {
        "ref": "U1",
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        "footprint": "Fuse:Fuse_1206_3216Metric",
        "x": 125,
        "y": 35,
        "pins": [("1", "IN", "PD_NEGOTIATED_VBUS"), ("2", "OUT", "PD_FUSED")],
    },
    {
        "ref": "U2",
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        "footprint": "Inductor_SMD:L_10.4x10.4_H4.8",
        "x": 205,
        "y": 35,
        "pins": [("1", "SW", "BUCK_SW"), ("2", "OUT", "FUSED_5V1")],
    },
    {
        "ref": "D2",
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        "footprint": "Diode_SMD:D_SMA",
        "x": 205,
        "y": 50,
        "pins": [("K", "K", "BUCK_SW"), ("A", "A", "GND")],
    },
    {
        "ref": "CIN1",
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        "footprint": "Capacitor_SMD:C_1206_3216Metric",
        "x": 145,
        "y": 70,
        "pins": [("1", "+", "PD_FUSED"), ("2", "-", "GND")],
    },
    {
        "ref": "CIN2",
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        "footprint": "Capacitor_SMD:C_1206_3216Metric",
        "x": 160,
        "y": 70,
        "pins": [("1", "+", "PD_FUSED"), ("2", "-", "GND")],
    },
    {
        "ref": "CBOOT",
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        "footprint": "Capacitor_SMD:C_0603_1608Metric",
        "x": 185,
        "y": 70,
        "pins": [("1", "BOOT", "BUCK_BOOT"), ("2", "SW", "BUCK_SW")],
    },
    {
        "ref": "CSS",
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        "footprint": "Capacitor_SMD:C_0603_1608Metric",
        "x": 200,
        "y": 70,
        "pins": [("1", "SS", "BUCK_SS"), ("2", "GND", "GND")],
    },
    {"ref": "REN1", "value": "665k", "footprint": "Resistor_SMD:R_0603_1608Metric", "x": 185, "y": 85, "pins": [("1", "VIN", "PD_FUSED"), ("2", "EN", "BUCK_EN")]},
    {"ref": "REN2", "value": "130k", "footprint": "Resistor_SMD:R_0603_1608Metric", "x": 200, "y": 85, "pins": [("1", "EN", "BUCK_EN"), ("2", "GND", "GND")]},
    {"ref": "RCOMP1", "value": "37.4k", "footprint": "Resistor_SMD:R_0603_1608Metric", "x": 215, "y": 85, "pins": [("1", "COMP", "BUCK_COMP"), ("2", "NODE", "BUCK_COMP_RC")]},
    {"ref": "CCOMP1", "value": "2200pF", "footprint": "Capacitor_SMD:C_0603_1608Metric", "x": 230, "y": 85, "pins": [("1", "NODE", "BUCK_COMP_RC"), ("2", "GND", "GND")]},
    {"ref": "CCOMP2", "value": "22pF", "footprint": "Capacitor_SMD:C_0603_1608Metric", "x": 245, "y": 85, "pins": [("1", "COMP", "BUCK_COMP"), ("2", "GND", "GND")]},
    {"ref": "CIN3", "value": "10nF 50V", "footprint": "Capacitor_SMD:C_0603_1608Metric", "x": 260, "y": 85, "pins": [("1", "+", "PD_FUSED"), ("2", "-", "GND")]},
    {
        "ref": "COUT1",
        "value": "47uF 10V",
        "footprint": "Capacitor_SMD:C_1210_3225Metric",
        "x": 230,
        "y": 35,
        "pins": [("1", "+", "FUSED_5V1"), ("2", "-", "GND")],
    },
    {
        "ref": "COUT2",
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        "footprint": "Capacitor_SMD:C_1210_3225Metric",
        "x": 245,
        "y": 35,
        "pins": [("1", "+", "FUSED_5V1"), ("2", "-", "GND")],
    },
    {
        "ref": "RFB1",
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        "footprint": "Resistor_SMD:R_0603_1608Metric",
        "x": 230,
        "y": 58,
        "pins": [("1", "TOP", "FUSED_5V1"), ("2", "FB", "BUCK_FB")],
    },
    {
        "ref": "RFB2",
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        "footprint": "Resistor_SMD:R_0603_1608Metric",
        "x": 245,
        "y": 58,
        "pins": [("1", "FB", "BUCK_FB"), ("2", "GND", "GND")],
    },
    {
        "ref": "Q1",
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        "footprint": "Package_SO:SOIC-8_3.9x4.9mm_P1.27mm",
        "x": 270,
        "y": 35,
        "pins": [("S", "SOURCE", "FUSED_5V1"), ("D", "DRAIN", "OPI_5V_SW"), ("G", "GATE", "PWR_GATE")],
    },
    {
        "ref": "Q2",
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        "footprint": "Package_TO_SOT_SMD:SOT-23",
        "x": 270,
        "y": 60,
        "pins": [("D", "DRAIN", "PWR_GATE"), ("S", "SOURCE", "GND"), ("G", "GATE", "Q2_GATE")],
    },
    {"ref": "R2", "value": "100k", "footprint": "Resistor_SMD:R_0603_1608Metric", "x": 290, "y": 45, "pins": [("1", "5V1", "FUSED_5V1"), ("2", "GATE", "PWR_GATE")]},
    {"ref": "R3", "value": "1k", "footprint": "Resistor_SMD:R_0603_1608Metric", "x": 290, "y": 60, "pins": [("1", "PICO", "PICO_GP15"), ("2", "Q2G", "Q2_GATE")]},
    {"ref": "R4", "value": "100k", "footprint": "Resistor_SMD:R_0603_1608Metric", "x": 290, "y": 72, "pins": [("1", "Q2G", "Q2_GATE"), ("2", "GND", "GND")]},
    {"ref": "C1", "value": "470uF-1000uF 10V", "footprint": "Capacitor_THT:CP_Radial_D10.0mm_P5.00mm", "x": 300, "y": 35, "pins": [("1", "+", "OPI_5V_SW"), ("2", "-", "GND")]},
    {
        "ref": "J1",
        "value": "Orange Pi Zero 3 26-pin",
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        "footprint": "Connector_PinHeader_2.54mm:PinHeader_1x09_P2.54mm_Vertical",
        "x": 135,
        "y": 120,
        "pins": [("1", "VDD", "OPI_3V3"), ("2", "GND", "GND"), ("3", "SDA", "OPI_SDA"), ("4", "SCL", "OPI_SCL"), ("5", "ADDR", "GND"), ("6", "A0", "PH_AIN"), ("7", "A1", "TDS_AIN"), ("8", "A2", "TURB_AIN"), ("9", "A3", "ORP_AIN")],
    },
    {
        "ref": "J4",
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        "footprint": "Connector_PinHeader_2.54mm:PinHeader_1x09_P2.54mm_Vertical",
        "x": 170,
        "y": 120,
        "pins": [("1", "VDD", "OPI_3V3"), ("2", "GND", "GND"), ("3", "SDA", "OPI_SDA"), ("4", "SCL", "OPI_SCL"), ("5", "ADDR", "OPI_3V3"), ("6", "A0", "DO_AIN"), ("7", "A1", "NH4_AIN"), ("8", "A2", "SPARE_AIN2"), ("9", "A3", "SPARE_AIN3")],
    },
    {"ref": "J5", "value": "DS18B20 water temp", "footprint": "Connector_PinHeader_2.54mm:PinHeader_1x03_P2.54mm_Vertical", "x": 210, "y": 115, "pins": [("1", "VCC", "OPI_3V3"), ("2", "DATA", "OPI_1WIRE"), ("3", "GND", "GND")]},
    {"ref": "R1", "value": "4.7k", "footprint": "Resistor_THT:R_Axial_DIN0207_L6.3mm_D2.5mm_P7.62mm_Horizontal", "x": 210, "y": 133, "pins": [("1", "3V3", "OPI_3V3"), ("2", "DATA", "OPI_1WIRE")]},
    {"ref": "J6", "value": "BME280 air sensor", "footprint": "Connector_PinHeader_2.54mm:PinHeader_1x04_P2.54mm_Vertical", "x": 245, "y": 115, "pins": [("1", "VCC", "OPI_3V3"), ("2", "GND", "GND"), ("3", "SDA", "OPI_SDA"), ("4", "SCL", "OPI_SCL")]},
    {"ref": "J7", "value": "DS3231 RTC", "footprint": "Connector_PinHeader_2.54mm:PinHeader_1x04_P2.54mm_Vertical", "x": 280, "y": 115, "pins": [("1", "VCC", "PICO_3V3"), ("2", "GND", "GND"), ("3", "SDA", "PICO_GP4"), ("4", "SCL", "PICO_GP5")]},
    {"ref": "J15", "value": "Download button", "footprint": "Connector_PinHeader_2.54mm:PinHeader_1x04_P2.54mm_Vertical", "x": 315, "y": 115, "pins": [("1", "NO", "PICO_GP14"), ("2", "C", "GND"), ("3", "LED+", "BUTTON_LED_A"), ("4", "LED-", "GND")]},
    {"ref": "R5", "value": "330R if 3.3V LED", "footprint": "Resistor_SMD:R_0603_1608Metric", "x": 315, "y": 133, "pins": [("1", "PICO", "PICO_LED_GP16"), ("2", "LED+", "BUTTON_LED_A")]},
    {"ref": "J16", "value": "Spare analog header", "footprint": "Connector_PinHeader_2.54mm:PinHeader_1x04_P2.54mm_Vertical", "x": 315, "y": 155, "pins": [("1", "3V3", "OPI_3V3"), ("2", "GND", "GND"), ("3", "AIN2", "SPARE_AIN2"), ("4", "AIN3", "SPARE_AIN3")]},
    {"ref": "J8", "value": "pH sensor", "footprint": "TerminalBlock_Phoenix:TerminalBlock_Phoenix_MKDS-1,5-3-5.08_1x03_P5.08mm_Horizontal", "x": 30, "y": 190, "pins": [("1", "5V", "OPI_5V_SW"), ("2", "GND", "GND"), ("3", "AO", "PH_AIN")]},
    {"ref": "J9", "value": "TDS sensor", "footprint": "TerminalBlock_Phoenix:TerminalBlock_Phoenix_MKDS-1,5-3-5.08_1x03_P5.08mm_Horizontal", "x": 70, "y": 190, "pins": [("1", "5V", "OPI_5V_SW"), ("2", "GND", "GND"), ("3", "AO", "TDS_AIN")]},
    {"ref": "J10", "value": "Turbidity sensor", "footprint": "TerminalBlock_Phoenix:TerminalBlock_Phoenix_MKDS-1,5-3-5.08_1x03_P5.08mm_Horizontal", "x": 110, "y": 190, "pins": [("1", "5V", "OPI_5V_SW"), ("2", "GND", "GND"), ("3", "AO", "TURB_AIN")]},
    {"ref": "J11", "value": "ORP sensor", "footprint": "TerminalBlock_Phoenix:TerminalBlock_Phoenix_MKDS-1,5-3-5.08_1x03_P5.08mm_Horizontal", "x": 150, "y": 190, "pins": [("1", "5V", "OPI_5V_SW"), ("2", "GND", "GND"), ("3", "AO", "ORP_AIN")]},
    {"ref": "J12", "value": "Dissolved oxygen", "footprint": "TerminalBlock_Phoenix:TerminalBlock_Phoenix_MKDS-1,5-3-5.08_1x03_P5.08mm_Horizontal", "x": 190, "y": 190, "pins": [("1", "5V", "OPI_5V_SW"), ("2", "GND", "GND"), ("3", "AO", "DO_AIN")]},
    {"ref": "J13", "value": "NH4 ISE amp", "footprint": "TerminalBlock_Phoenix:TerminalBlock_Phoenix_MKDS-1,5-3-5.08_1x03_P5.08mm_Horizontal", "x": 230, "y": 190, "pins": [("1", "5V", "OPI_5V_SW"), ("2", "GND", "GND"), ("3", "AO", "NH4_AIN")]},
]


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
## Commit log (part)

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2026-05-12 Initial water logger project
2026-05-12 Tidy wiring diagram
2026-05-12 Rotate logs by week
2026-05-12 Add Bluetooth phone download and time sync workflow
2026-05-12 Add Android Bluetooth companion app
2026-05-12 Add Bluetooth live readings
2026-05-14 Fix Android Bluetooth permissions
2026-05-14 Document relay and MOS power switch wiring
2026-05-14 Add button pairing mode
2026-05-14 Increase manual power off hold time
2026-05-14 Handle Bluetooth client disconnects
2026-05-14 Improve Android app interface
2026-05-14 Add Android sensor section dashboard
2026-05-14 Add Orange Pi 5 Max EC25-AU variant
2026-05-14 Add cellular SMS and server alerts
2026-05-14 Clarify compact M2 modem carrier
2026-05-14 Make alert SMS numbers configurable
2026-05-14 Baseline installed sensors for alerts
2026-05-14 Add signal status and test SMS controls
2026-05-24 Fix logger review issues
2026-05-24 Support both Orange Pi boards with optional cellular
2026-05-24 Clean up main docs and wiring diagram
2026-05-24 Add project design brief to README
2026-05-24 Add Android launcher icon
2026-05-24 Add PCB carrier design brief
2026-05-24 Add Zero 3 PCB carrier scaffold
2026-05-24 Ignore KiCad PCB lock files
2026-05-25 Add schematic synced Zero 3 carrier PCB draft
